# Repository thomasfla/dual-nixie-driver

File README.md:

# dual-nixie-driver

A simple board, driving 2 nixies from discrete transistors and a Atmega8.

# Licence 
This all project is under (CC BY-SA 3.0) licence in the Open Source Hardware spirit https://www.oshwa.org/
All help or comment are wellcome; 
See more here https://hackaday.io/project/69708

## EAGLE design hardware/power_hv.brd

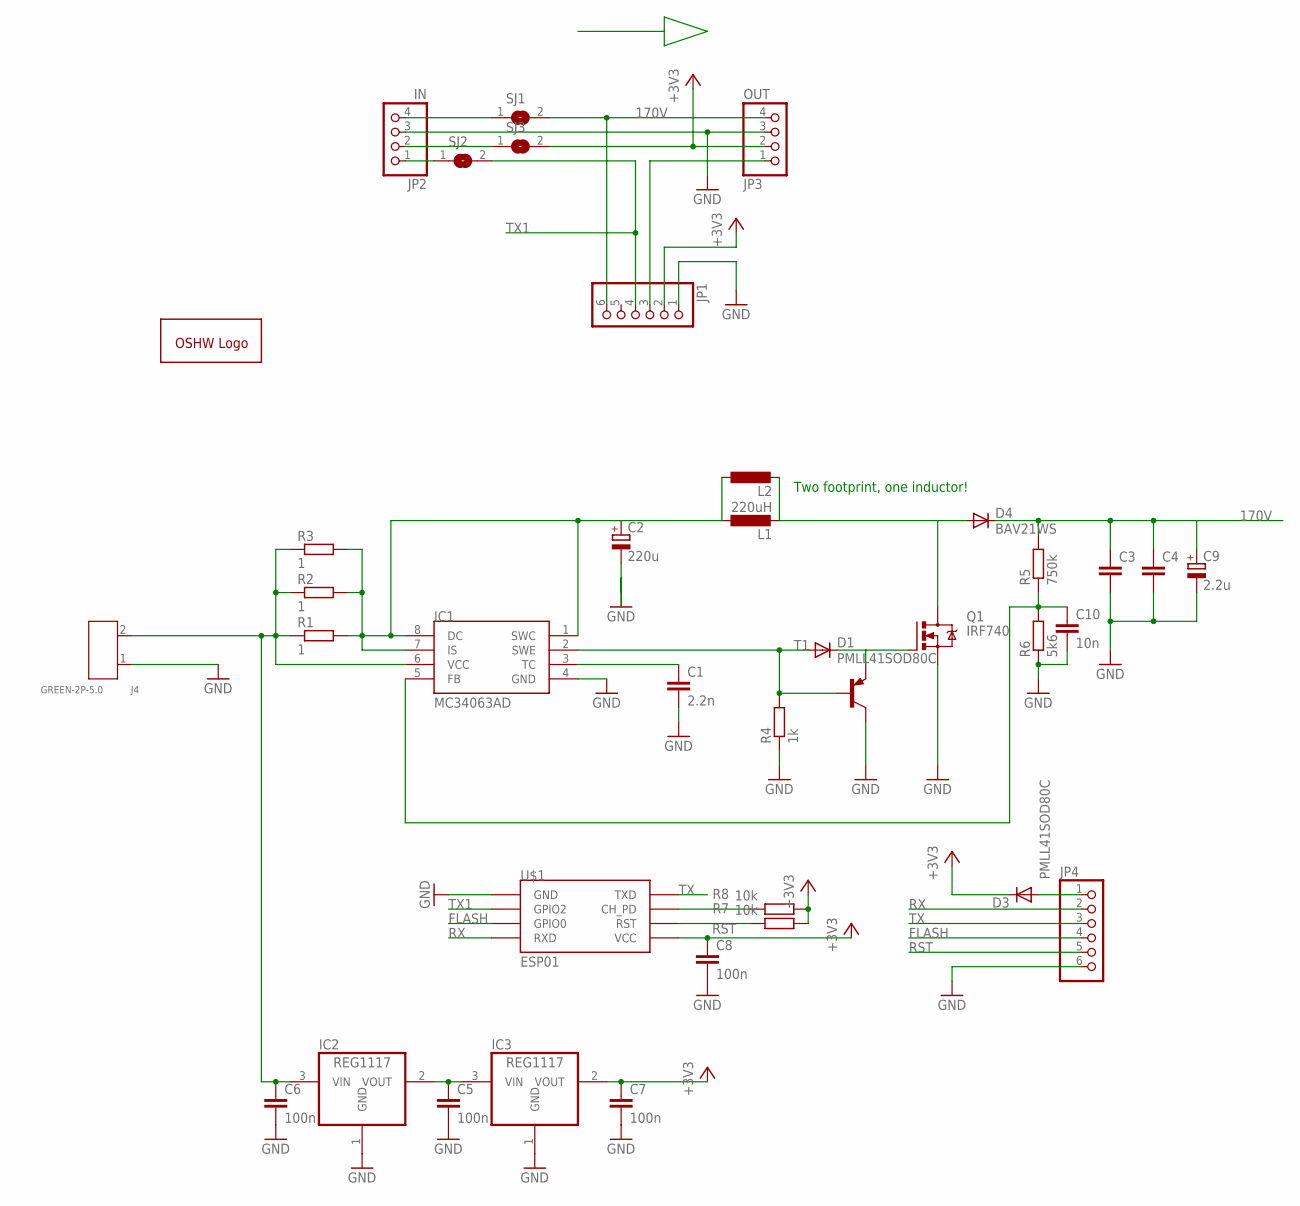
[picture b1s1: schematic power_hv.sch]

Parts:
C1: 2.2n; C0805
C2: 220u; 140CLH-0810
C3, C4: C-EUC1210K; C1210K
C5, C6, C7, C8: 100n; C0805
C9: 2.2u; E5-8,5
C10: 10n; C0805
D1, D3: PMLL41SOD80C; SOD80C
D4: BAV21WS; SOD323-W
GOLD_ORB_SM1: OSHWLOGOLOGO8MM; OSHW_8MM
IC1: MC34063AD; SOIC8
IC2, IC3: REG1117; SOT223
J4: GREEN-2P-5.0; H2-5.0-10.5X8.0MM
JP1, JP4: PINHD-1X6; 1X06
JP2: IN; 1X04
JP3: OUT; 1X04
L1: 220uH; POWER-CHOKE_WE-TPC
L2: L-EU6000-XXX-RC; 6000-XXXX-RC
Q1: IRF740; TO220BV
R1, R2, R3: 1; R0805
R4: 1k; R0805
R5: 750k; R0805
R6: 5k6; R0805
R7, R8: 10k; R0805
SJ1, SJ2, SJ3: SJ
T1: BC807-40-PNP-SOT23-BEC; SOT23-BEC
U$1: ESP01

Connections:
170V: C3.1, C4.1, C9.+, D4.C, JP1.6, JP3.4, R5.2, SJ1.2
+3V3: C7.1, C8.1, D3.C, IC3.2 (VOUT), JP1.2, JP3.2, R7.1, R8.1, SJ3.2, U$1.VCC
FLASH: JP4.4, U$1.GPIO0
GND: C1.2, C2.-, C3.2, C4.2, C5.2, C6.2, C7.2, C8.2, C9.-, C10.2, IC1.4 (GND), IC2.1 (GND), IC3.1 (GND), J4.1, JP1.1, JP2.3, JP3.3, JP4.6, Q1.S, R4.1, R6.1, T1.C, U$1.GND
unnamed: C2.+, IC1.1 (SWC), IC1.7 (IS), IC1.8 (DC), L1.1, L2.1, R1.2, R2.2, R3.2
unnamed: D1.A, IC1.2 (SWE), R4.2, T1.B
unnamed: C1.1, IC1.3 (TC)
unnamed: JP1.3, JP3.1
unnamed: C6.1, IC1.6 (VCC), IC2.3 (VIN), J4.2, R1.1, R2.1, R3.1
unnamed: D1.C, Q1.G, T1.E
unnamed: D4.A, L1.2, L2.2, Q1.D
unnamed: C10.1, IC1.5 (FB), R5.1, R6.2
unnamed: C5.1, IC2.2 (VOUT), IC3.3 (VIN)
unnamed: R8.2, U$1.CH_PD
unnamed: D3.A, JP4.1
unnamed: JP2.4, SJ1.1
unnamed: JP2.2, SJ3.1
unnamed: JP2.1, SJ2.1
RST: JP4.5, R7.2, U$1.RST
RX: JP4.2, U$1.RX (RXD)
TX: JP4.3, U$1.TX (TXD)
TX1: JP1.4, SJ2.2, U$1.GPIO2

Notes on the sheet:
Two footprint, one inductor!

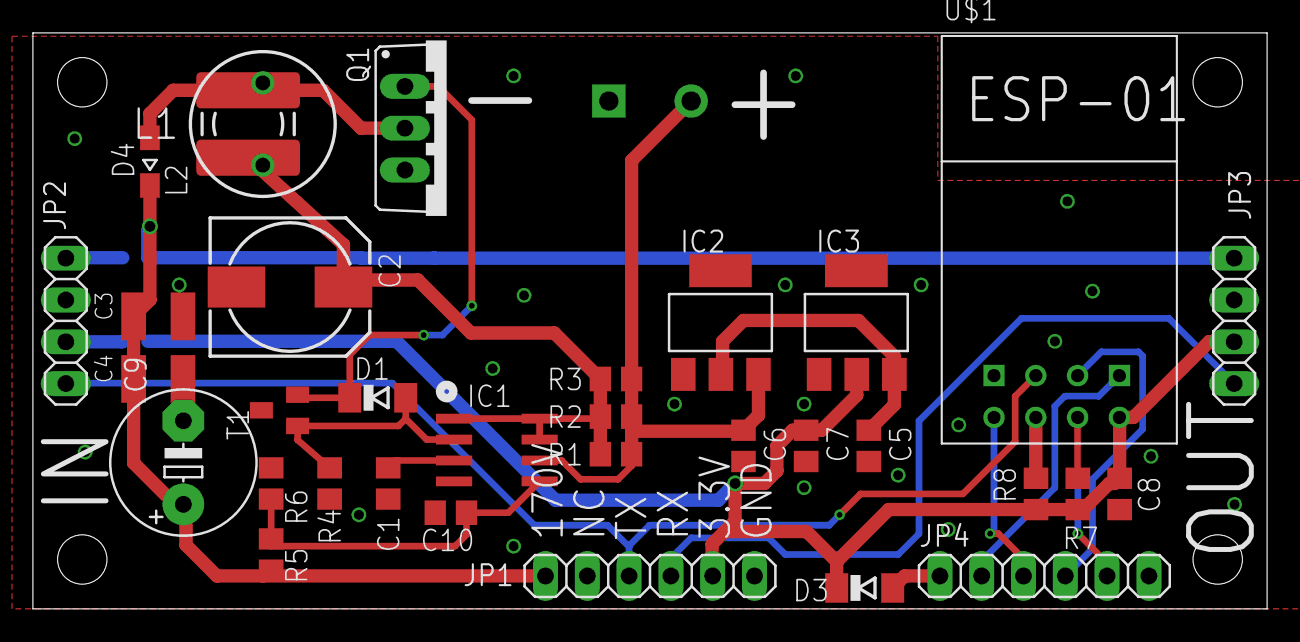
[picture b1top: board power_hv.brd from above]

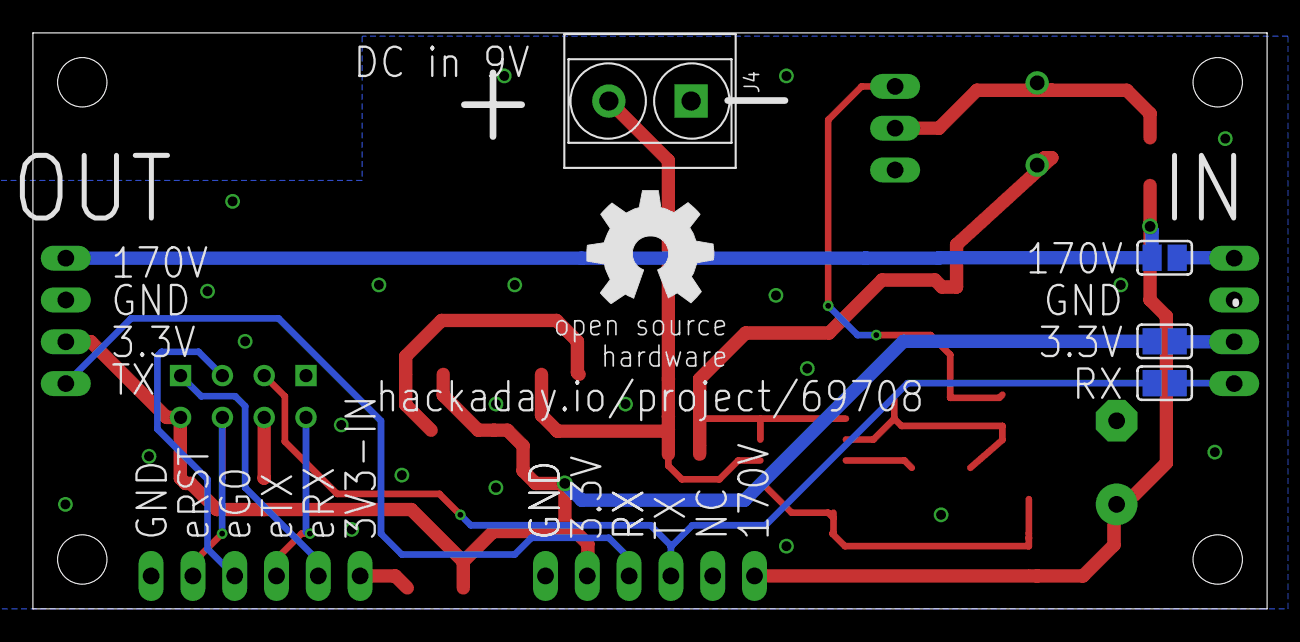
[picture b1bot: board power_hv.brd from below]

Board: 2 copper layers, 75.0 x 35.0 mm, 38 parts (5 on the bottom side), 22 nets.

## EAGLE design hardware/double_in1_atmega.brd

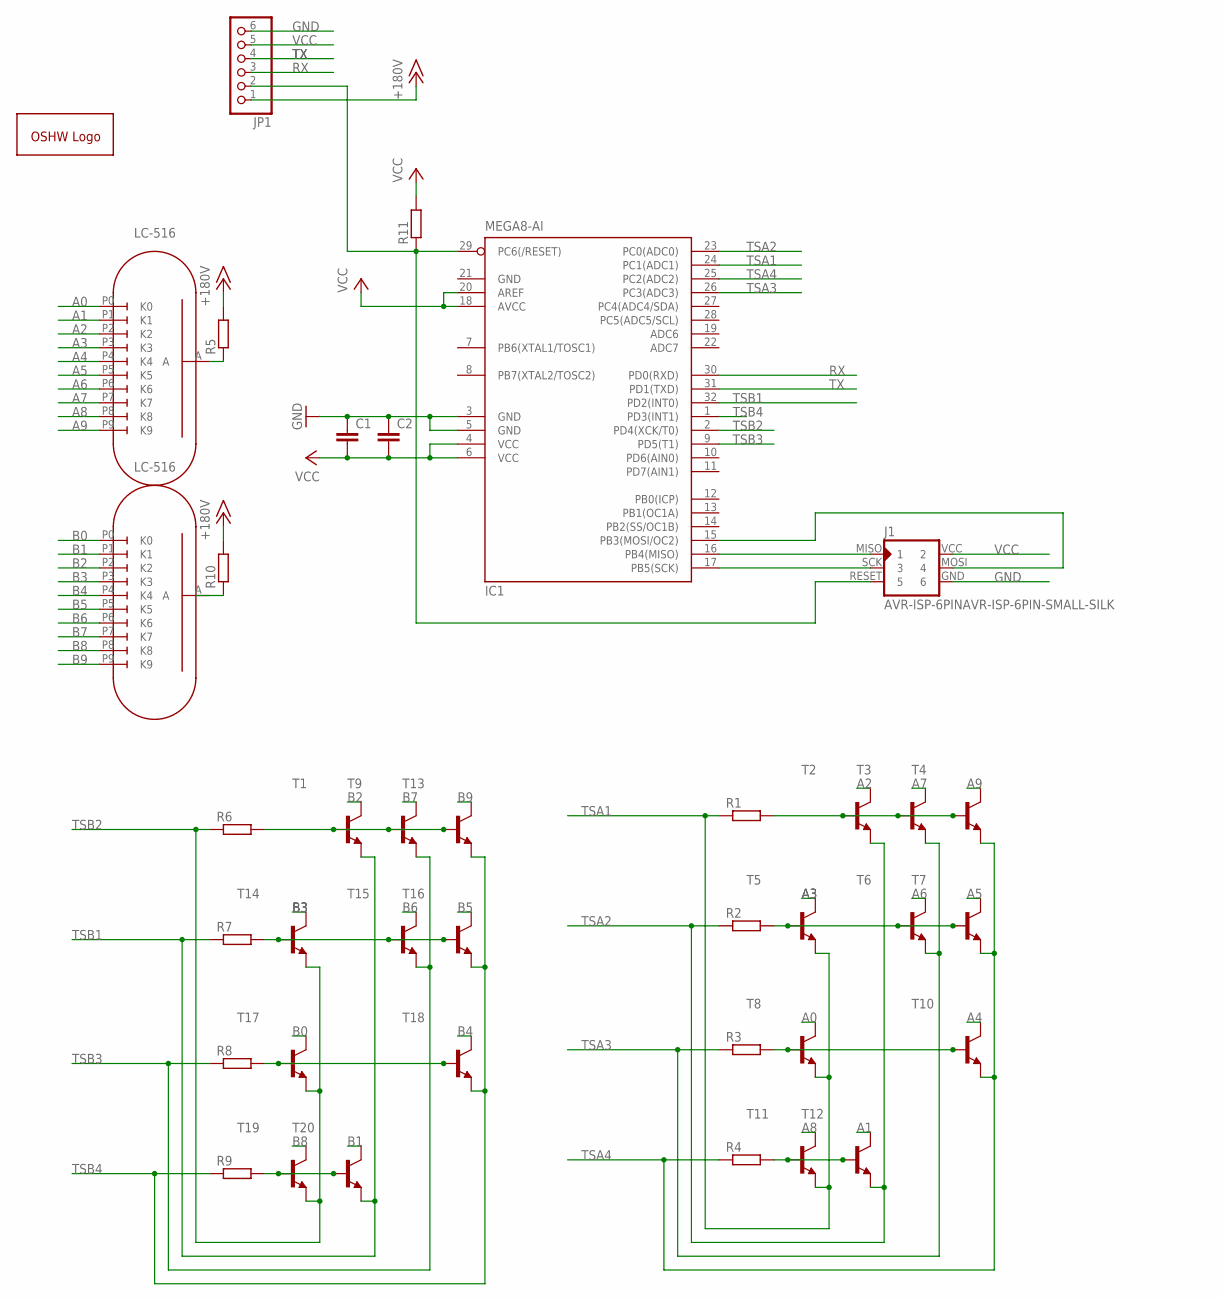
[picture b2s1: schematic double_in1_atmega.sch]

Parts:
C1, C2: C; C0805
GOLD_ORB_SM1: OSHWLOGOLOGO5MM; OSHW_5MM
IC1: MEGA8-AI; TQFP32-08
J1: AVR-ISP-6PINAVR-ISP-6PIN-SMALL-SILK; AVR-ISP-6PIN-SMAILL-SILK
JP1: PINHD-1X6; 1X06
R1, R2, R3, R4, R6, R7, R8, R9, R11: R-EU_R0603; R0603
R5, R10: R-EU_M1206; M1206
T1, T2, T3, T4, T5, T6, T7, T8, T9, T10, T11, T12, T13, T14, T15, T16, T17, T18, T19, T20: MMBTA42LT1-NPN-SOT23-BEC; SOT23-BEC
U$1, U$2: LC-516

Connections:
+15V: JP1.1, R5.2, R10.2
A0: T8.C, U$1.P0 (K0)
A1: T12.C, U$1.P1 (K1)
A2: T2.C, U$1.P2 (K2)
A3: T5.C, U$1.P3 (K3)
A4: T10.C, U$1.P4 (K4)
A5: T7.C, U$1.P5 (K5)
A6: T6.C, U$1.P6 (K6)
A7: T3.C, U$1.P7 (K7)
A8: T11.C, U$1.P8 (K8)
A9: T4.C, U$1.P9 (K9)
B0: T17.C, U$2.P0 (K0)
B1: T20.C, U$2.P1 (K1)
B2: T1.C, U$2.P2 (K2)
B3: T14.C, U$2.P3 (K3)
B4: T18.C, U$2.P4 (K4)
B5: T16.C, U$2.P5 (K5)
B6: T15.C, U$2.P6 (K6)
B7: T9.C, U$2.P7 (K7)
B8: T19.C, U$2.P8 (K8)
B9: T13.C, U$2.P9 (K9)
GND: C1.1, C2.1, IC1.3 (GND), IC1.5 (GND), IC1.21 (GND), J1.GND (6), JP1.6
unnamed: R10.1, U$2.A
unnamed: IC1.29 (PC6(/RESET)), J1.RESET (5), JP1.2, R11.1
unnamed: R5.1, U$1.A
unnamed: IC1.16 (PB4(MISO)), J1.MISO (1)
unnamed: IC1.17 (PB5(SCK)), J1.SCK (3)
unnamed: IC1.15 (PB3(MOSI/OC2)), J1.MOSI (4)
unnamed: R6.2, T1.B, T9.B, T13.B
unnamed: R9.2, T19.B, T20.B
unnamed: R7.2, T14.B, T15.B, T16.B
unnamed: R4.2, T11.B, T12.B
unnamed: R8.2, T17.B, T18.B
unnamed: R3.2, T8.B, T10.B
unnamed: R2.2, T5.B, T6.B, T7.B
unnamed: R1.2, T2.B, T3.B, T4.B
RX: IC1.30 (PD0(RXD)), JP1.3
TSA1: IC1.24 (PC1(ADC1)), R1.1, T5.E, T8.E, T11.E
TSA2: IC1.23 (PC0(ADC0)), R2.1, T2.E, T12.E
TSA3: IC1.26 (PC3(ADC3)), R3.1, T3.E, T6.E
TSA4: IC1.25 (PC2(ADC2)), R4.1, T4.E, T7.E, T10.E
TSB1: IC1.32 (PD2(INT0)), R7.1, T1.E, T20.E
TSB2: IC1.2 (PD4(XCK/T0)), R6.1, T14.E, T17.E, T19.E
TSB3: IC1.9 (PD5(T1)), R8.1, T9.E, T15.E
TSB4: IC1.1 (PD3(INT1)), R9.1, T13.E, T16.E, T18.E
TX: IC1.31 (PD1(TXD)), JP1.4
VCC: C1.2, C2.2, IC1.4 (VCC), IC1.6 (VCC), IC1.18 (AVCC), IC1.20 (AREF), J1.VCC (2), JP1.5, R11.2

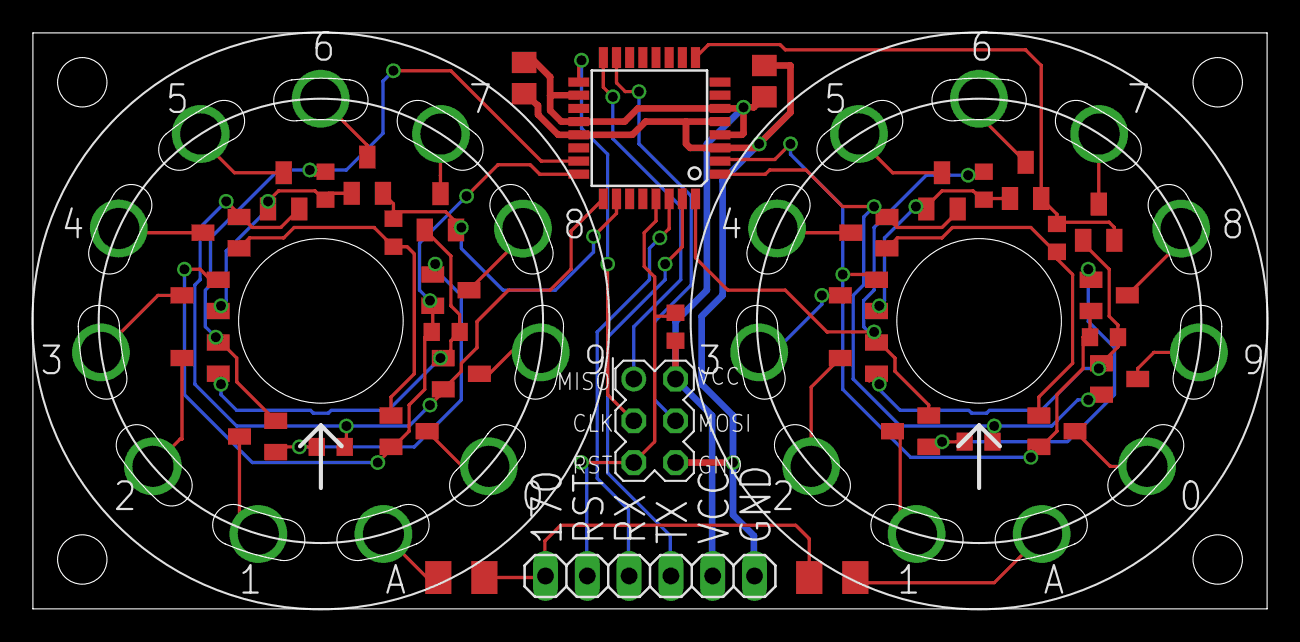
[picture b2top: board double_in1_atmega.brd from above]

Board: 2 copper layers, 75.0 x 35.0 mm, 39 parts (1 on the bottom side), 47 nets.

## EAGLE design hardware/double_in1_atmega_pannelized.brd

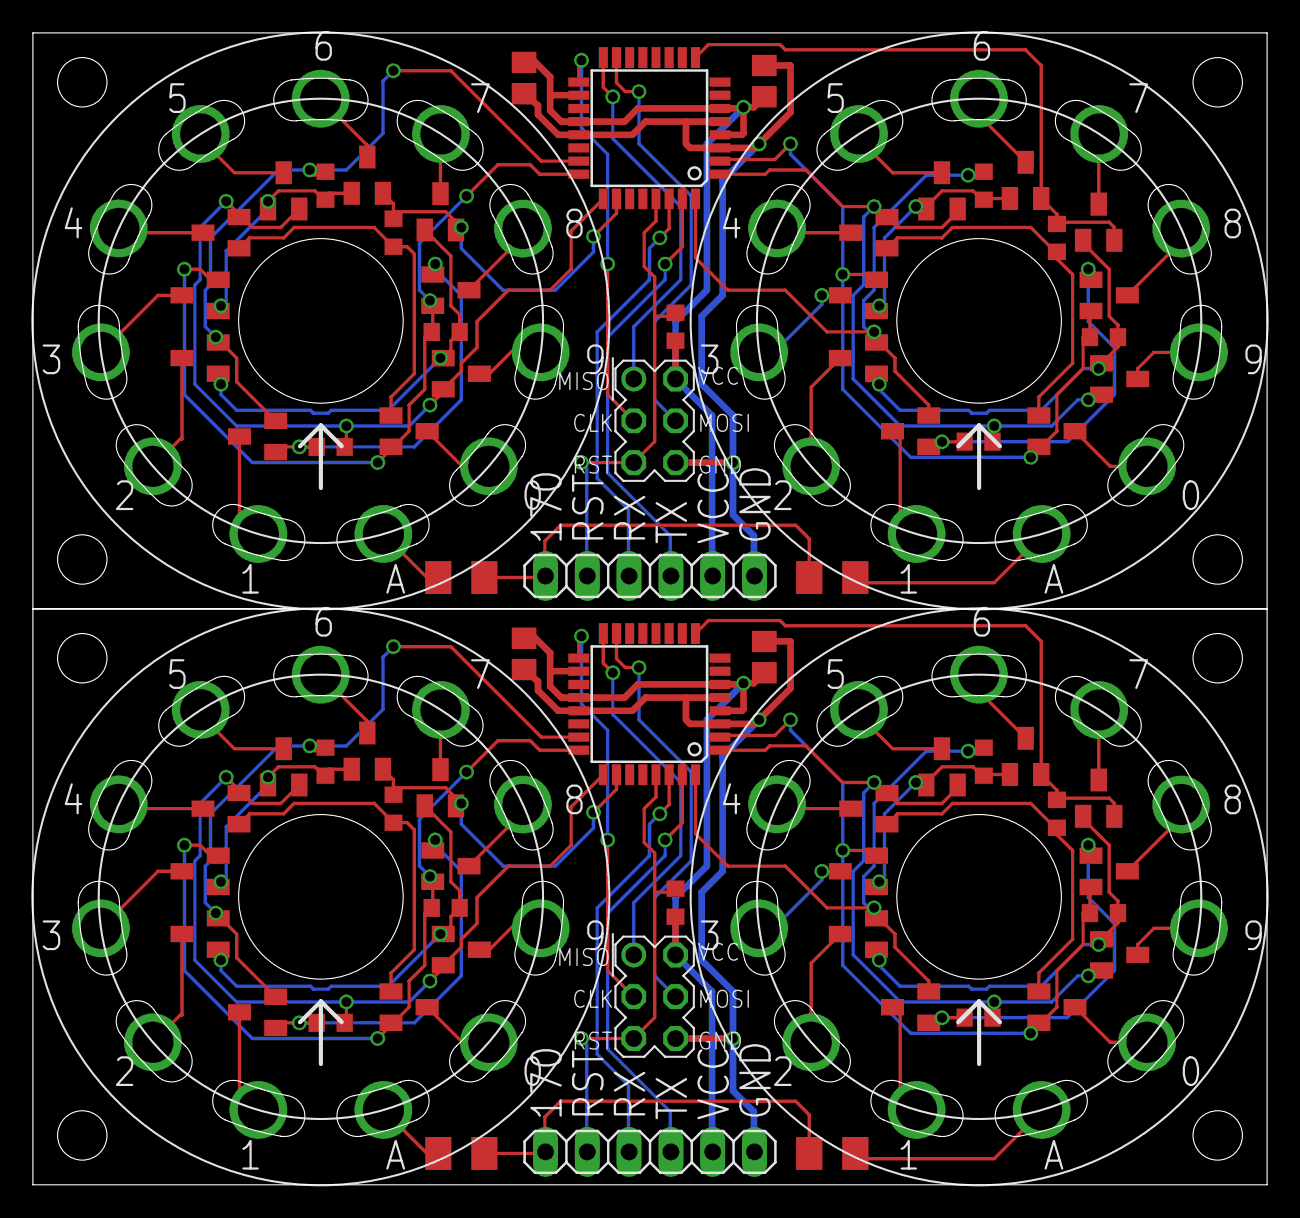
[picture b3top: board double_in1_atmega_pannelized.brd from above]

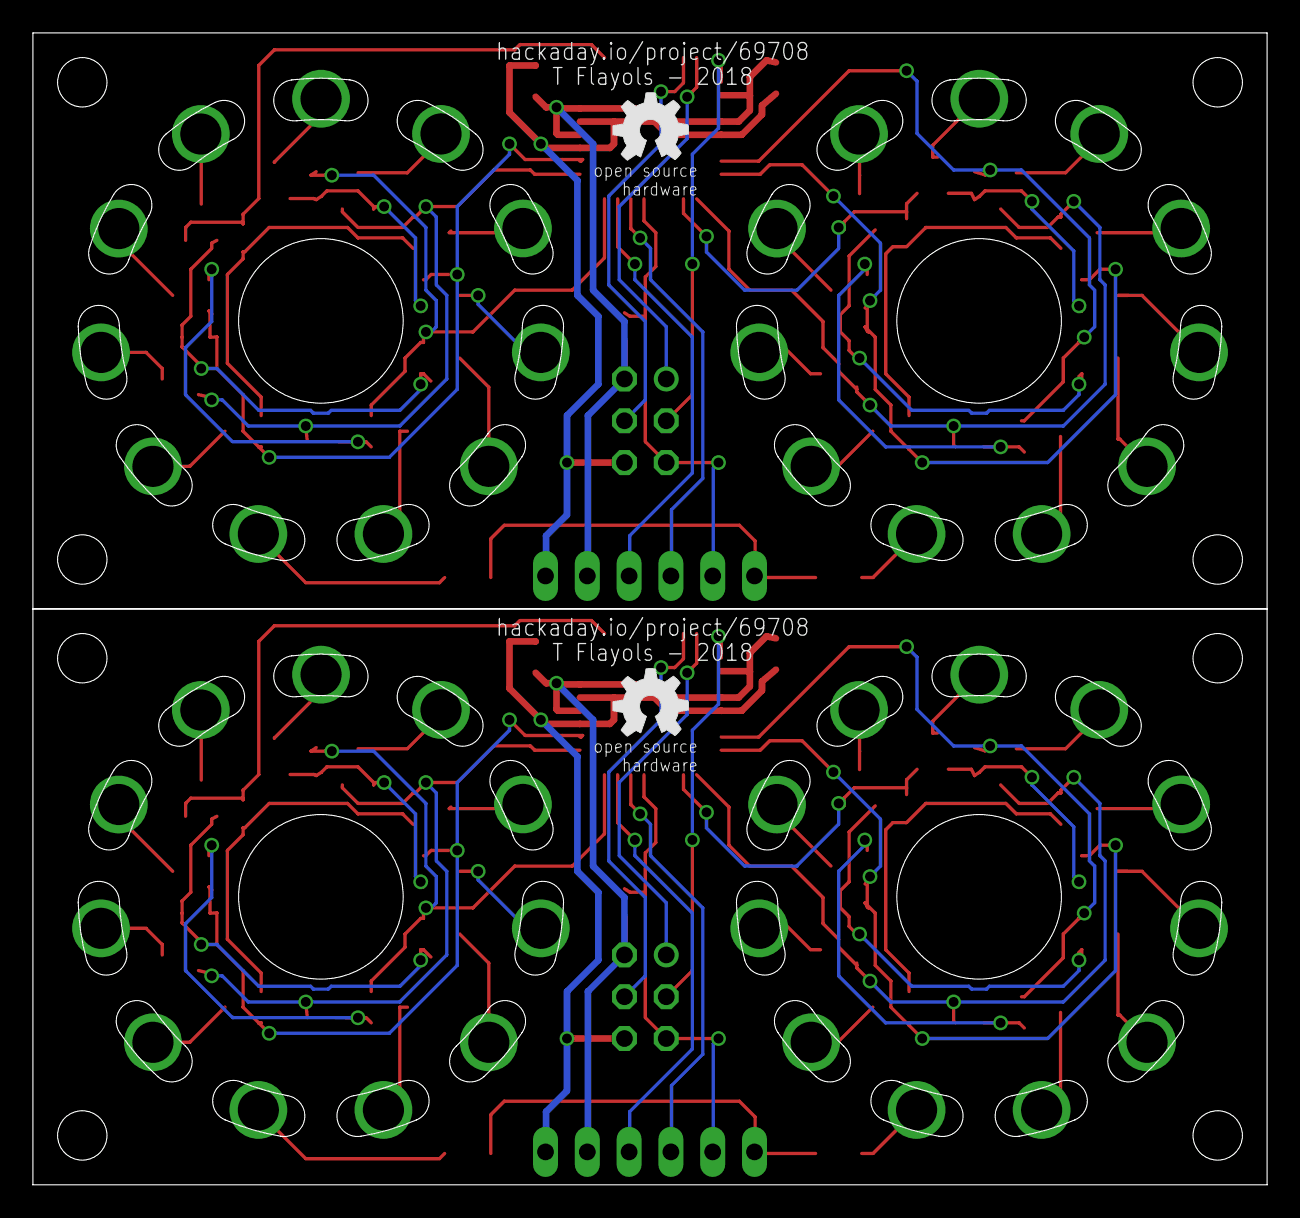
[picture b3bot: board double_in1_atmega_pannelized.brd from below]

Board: 2 copper layers, 75.0 x 70.0 mm, 78 parts (2 on the bottom side), 94 nets.

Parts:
C1, C2, C3, C4: C0805
GOLD_ORB_SM1, GOLD_ORB_SM2: OSHWLOGOLOGO5MM; OSHW_5MM
IC1, IC2: MEGA8-AI; TQFP32-08
J1, J2: AVR-ISP-6PINAVR-ISP-6PIN-SMALL-SILK; AVR-ISP-6PIN-SMAILL-SILK
JP1, JP2: 1X06
R1, R2, R3, R4, R6, R7, R8, R9, R11, R12, R13, R14, R15, R17, R18, R19, R20, R22: R0603
R5, R10, R16, R21: M1206
T1, T2, T3, T4, T5, T6, T7, T8, T9, T10, T11, T12, T13, T14, T15, T16, T17, T18, T19, T20, T21, T22, T23, T24, T25, T26, T27, T28, T29, T30, T31, T32, T33, T34, T35, T36, T37, T38, T39, T40: SOT23-BEC
U$1, U$2, U$3, U$4: LC-516

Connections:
+15V: JP1.1, R5.2, R10.2
+15V1: JP2.1, R16.2, R21.2
A0: T8.C, U$1.P0
A1: T12.C, U$1.P1
A2: T2.C, U$1.P2
A3: T5.C, U$1.P3
A4: T10.C, U$1.P4
A5: T7.C, U$1.P5
A6: T6.C, U$1.P6
A7: T3.C, U$1.P7
A8: T11.C, U$1.P8
A9: T4.C, U$1.P9
A10: T30.C, U$3.P1
A11: T21.C, U$3.P2
A12: T24.C, U$3.P3
A13: T28.C, U$3.P4
A14: T26.C, U$3.P5
A15: T25.C, U$3.P6
A16: T22.C, U$3.P7
A17: T29.C, U$3.P8
A18: T23.C, U$3.P9
A19: T27.C, U$3.P0
B0: T17.C, U$2.P0
B1: T20.C, U$2.P1
B2: T1.C, U$2.P2
B3: T14.C, U$2.P3
B4: T18.C, U$2.P4
B5: T16.C, U$2.P5
B6: T15.C, U$2.P6
B7: T9.C, U$2.P7
B8: T19.C, U$2.P8
B9: T13.C, U$2.P9
B10: T31.C, U$4.P2
B11: T32.C, U$4.P7
B12: T33.C, U$4.P9
B13: T34.C, U$4.P3
B14: T35.C, U$4.P6
B15: T36.C, U$4.P5
B16: T37.C, U$4.P0
B17: T38.C, U$4.P4
B18: T39.C, U$4.P8
B19: T40.C, U$4.P1
GND: C1.1, C2.1, IC1.3, IC1.5, IC1.21, J1.GND, JP1.6
GND1: C3.1, C4.1, IC2.3, IC2.5, IC2.21, J2.GND, JP2.6
unnamed: R10.1, U$2.A
unnamed: IC1.29, J1.RESET, JP1.2, R11.1
unnamed: R16.1, U$3.A
unnamed: R5.1, U$1.A
unnamed: IC1.16, J1.MISO
unnamed: IC2.29, J2.RESET, JP2.2, R22.1
unnamed: R21.1, U$4.A
unnamed: IC2.16, J2.MISO
unnamed: IC1.17, J1.SCK
unnamed: IC1.15, J1.MOSI
unnamed: R6.2, T1.B, T9.B, T13.B
unnamed: R9.2, T19.B, T20.B
unnamed: R7.2, T14.B, T15.B, T16.B
unnamed: R4.2, T11.B, T12.B
unnamed: R8.2, T17.B, T18.B
unnamed: R3.2, T8.B, T10.B
unnamed: R2.2, T5.B, T6.B, T7.B
unnamed: R1.2, T2.B, T3.B, T4.B
unnamed: IC2.17, J2.SCK
unnamed: IC2.15, J2.MOSI
unnamed: R17.2, T31.B, T32.B, T33.B
unnamed: R20.2, T39.B, T40.B
unnamed: R19.2, T37.B, T38.B
unnamed: R18.2, T34.B, T35.B, T36.B
unnamed: R15.2, T29.B, T30.B
unnamed: R14.2, T27.B, T28.B
unnamed: R13.2, T24.B, T25.B, T26.B
unnamed: R12.2, T21.B, T22.B, T23.B
RX: IC1.30, JP1.3
RX1: IC2.30, JP2.3
TSA1: IC1.24, R1.1, T5.E, T8.E, T11.E
TSA2: IC1.23, R2.1, T2.E, T12.E
TSA3: IC1.26, R3.1, T3.E, T6.E
TSA4: IC1.25, R4.1, T4.E, T7.E, T10.E
TSA5: IC2.23, R13.1, T21.E, T30.E
TSA6: IC2.26, R14.1, T22.E, T25.E
TSA7: IC2.25, R15.1, T23.E, T26.E, T28.E
TSA8: IC2.24, R12.1, T24.E, T27.E, T29.E
TSB1: IC1.32, R7.1, T1.E, T20.E
TSB2: IC1.2, R6.1, T14.E, T17.E, T19.E
TSB3: IC1.9, R8.1, T9.E, T15.E
TSB4: IC1.1, R9.1, T13.E, T16.E, T18.E
TSB5: IC2.32, R18.1, T31.E, T40.E
TSB6: IC2.2, R17.1, T34.E, T37.E, T39.E
TSB7: IC2.9, R19.1, T32.E, T35.E
TSB8: IC2.1, R20.1, T33.E, T36.E, T38.E
TX: IC1.31, JP1.4
TX1: IC2.31, JP2.4
VCC: C1.2, C2.2, IC1.4, IC1.6, IC1.18, IC1.20, J1.VCC, JP1.5, R11.2
VCC1: C3.2, C4.2, IC2.4, IC2.6, IC2.18, IC2.20, J2.VCC, JP2.5, R22.2

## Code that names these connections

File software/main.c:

#include <avr/io.h>
#define F_CPU 8000000UL
#include <util/delay.h>
#define LED_PIN PB5
#define TX_PIN PD1
#define BAUD 9600                               	// define baud (9600:0.2%error)
#define BAUDRATE ((F_CPU)/(BAUD*16UL)-1)        	// set baud rate value for UBRR

#define sbi(port, bit) (port) |= (1 << (bit))
#define cbi(port, bit) (port) &= ~(1 << (bit))
#define TSA1 1 // PC1 
#define TSA2 0 // PC0
#define TSA3 3 // PC3
#define TSA4 2 // PC2

#define TSB1 4 // PD4
#define TSB2 2 // PD2
#define TSB3 5 // PD5
#define TSB4 3 // PD3
/*
noxtal @8MHz
avrdude -c usbasp -p m8 -U lfuse:w:0xE4:m -U hfuse:w:0xC4:m
*/

// function to initialize UART
void uart_init (void)
{
    UBRRH = (BAUDRATE>>8);
    UBRRL = BAUDRATE;                       	// set baud rate
    UCSRB|= (1<<TXEN)|(1<<RXEN);            	// enable RX and TX
    UCSRC|= (1<<URSEL)|(1<<UCSZ0)|(1<<UCSZ1);   // 8bit data format
}
//~ int setup(void);
int setup(void)
{
  /* Set LED_PIN to output. */
  //~ DDRB |= _BV(LED_PIN);  
  //~ DDRD |= _BV(TX_PIN);  
  
  uart_init();
  return 0;	
}

// function to send data
void uart_transmit (unsigned char data)
{
    while (!( UCSRA & (1<<UDRE)));            	// wait while register is free
    UDR = data;                               	// load data in the register
}
// function to receive data
unsigned char uart_received (void)
{
    while(!((UCSRA) & (1<<RXC)));               	// wait while data is being received
    return UDR;                               	// return 8-bit data
}

void set_to_1 (unsigned char *port,unsigned char *ddr,unsigned char bit)
{
  sbi(*ddr , bit); // output
  sbi(*port, bit); // 1
}
void set_to_0 (unsigned char *port,unsigned char *ddr,unsigned char bit)
{
  sbi(*ddr , bit); // output
  cbi(*port, bit); // 0
}
void set_to_Z (unsigned char *port,unsigned char *ddr,unsigned char bit)
{
  cbi(*ddr , bit); // input
  cbi(*port, bit); // no pull-up
}
void display_n(unsigned char n, unsigned char AB)
{
    unsigned char DDR  = (AB)?DDRC:DDRD;   //make a copy of current I/O register value
    unsigned char PORT = (AB)?PORTC:PORTD; //make a copy of current I/O register value
    unsigned char TS1  = (AB)?TSA1:TSB1;
    unsigned char TS2  = (AB)?TSA2:TSB2;
    unsigned char TS3  = (AB)?TSA3:TSB3;
    unsigned char TS4  = (AB)?TSA4:TSB4;
    //default all Z
    set_to_Z(&PORT,&DDR,TS1);
    set_to_Z(&PORT,&DDR,TS2);
    set_to_Z(&PORT,&DDR,TS3);
    set_to_Z(&PORT,&DDR,TS4);
    switch(n) {
        case 0:
          set_to_1(&PORT,&DDR,TS3);
          set_to_0(&PORT,&DDR,TS1);
        break; 
        case 1:
          set_to_1(&PORT,&DDR,TS4);
          set_to_0(&PORT,&DDR,TS2);
        break; 
        case 2:
          set_to_1(&PORT,&DDR,TS1);
          set_to_0(&PORT,&DDR,TS2);
        break; 
        case 3:
          set_to_1(&PORT,&DDR,TS2);
          set_to_0(&PORT,&DDR,TS1);
        break; 
        case 4:
          set_to_1(&PORT,&DDR,TS3);
          set_to_0(&PORT,&DDR,TS4);
        break; 
        case 5:
          set_to_1(&PORT,&DDR,TS2);
          set_to_0(&PORT,&DDR,TS4);
        break; 
        case 6:
          set_to_1(&PORT,&DDR,TS2);
          set_to_0(&PORT,&DDR,TS3);
        break; 
        case 7:
          set_to_1(&PORT,&DDR,TS1);
          set_to_0(&PORT,&DDR,TS3);
        break; 
        case 8:
          set_to_1(&PORT,&DDR,TS4);
          set_to_0(&PORT,&DDR,TS1);
        break; 
        case 9:
          set_to_1(&PORT,&DDR,TS1);
          set_to_0(&PORT,&DDR,TS4);
        break;
	case 10:
		//This is all off
	break;  
        default:
          set_to_1(&PORT,&DDR,TS3);
          set_to_0(&PORT,&DDR,TS1);
    }
    if (AB)  //apply I/O register value
    {
        DDRC = DDR;
        PORTC = PORT;
    }
    else
    {
        DDRD = DDR;
        PORTD = PORT;
    }
}

int main(void)
{	
	// setup
	setup();

    //test display 00 11 22 33 ..
    int i,j,k;

    //~ display_n(10,0);
	//~ while(1) // Dimming
	//~ {
		//~ for (j=0;j<50;j++)
		//~ {
			//~ for (i=0;i<10;i++)
			//~ {
				//~ for (k=0;k<50;k++)
				//~ {
					//~ if (k<j)
					 //~ {display_n(5,1);}
					//~ else
					 //~ {display_n(10,1);}
				//~ }
				//~ _delay_ms(1); 
			//~ }
		//~ }
		//~ for (j=0;j<50;j++)
		//~ {
			//~ for (i=0;i<10;i++)
			//~ {
				//~ for (k=0;k<50;k++)
				//~ {
					//~ if (k<j)
					 //~ {display_n(10,1);}
					//~ else
					 //~ {display_n(5,1);}
				//~ }
				//~ _delay_ms(1); 
			//~ }
		//~ }
	//~ }

    for (i=0;i<10;i++)
    {
        display_n(i,0);
        display_n(i,1);
        _delay_ms(500); 
    }

    for (i=0;i<100;i++)
    {
        display_n(i/10,0);
        display_n(i%10,1);
        _delay_ms(100); 
    }

	//daisy chain BCD format ends with 0xff
	// example: 12h30m59s will be:
	//      0x12 0x30 0x59 0xff
	// if this board is the first, it will transmit 
    //      0x12 0x30 0xff
    // and will display 
    //      (5)(9) 
    unsigned char rx_prev=0xf0; //0xf0 is a reserved value meaning empty
    unsigned char rx=0xf0; 
    while(1) 
    {
        rx_prev = rx;
        rx=uart_received();
        if (rx == 0xff) //it is the end
        { 
            uart_transmit(0xff);
            display_n((rx_prev>>4)&0x0F,0);
            display_n((rx_prev   )&0x0F,1);
            rx=0xf0;
        }
        else if(rx_prev!=0xf0)
        {
            uart_transmit(rx_prev);
        }
    }
	return 0;
}

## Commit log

2018-03-01 add files
2018-03-01 add picture
2018-03-25 [PCB] rev1; Change resistors size, center ATMEGA8, make slots for nixie alignment, minor changes
2018-08-17 add optional master board with esp8266 to drive the module and with 170V power supply
2018-08-17 generate gerber for jlpcb
2018-08-17 add clean scipt
2018-08-17 remove manualy panelize version since jlpcb does it for free
2018-08-17 add esp8266 clock firmware
2018-09-02 send on the two serials for compatibility with new board design
2018-09-02 set component values; add filter cap on power feedback
